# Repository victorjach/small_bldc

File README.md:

small_bldc
==========

Small Brushless Motor controller

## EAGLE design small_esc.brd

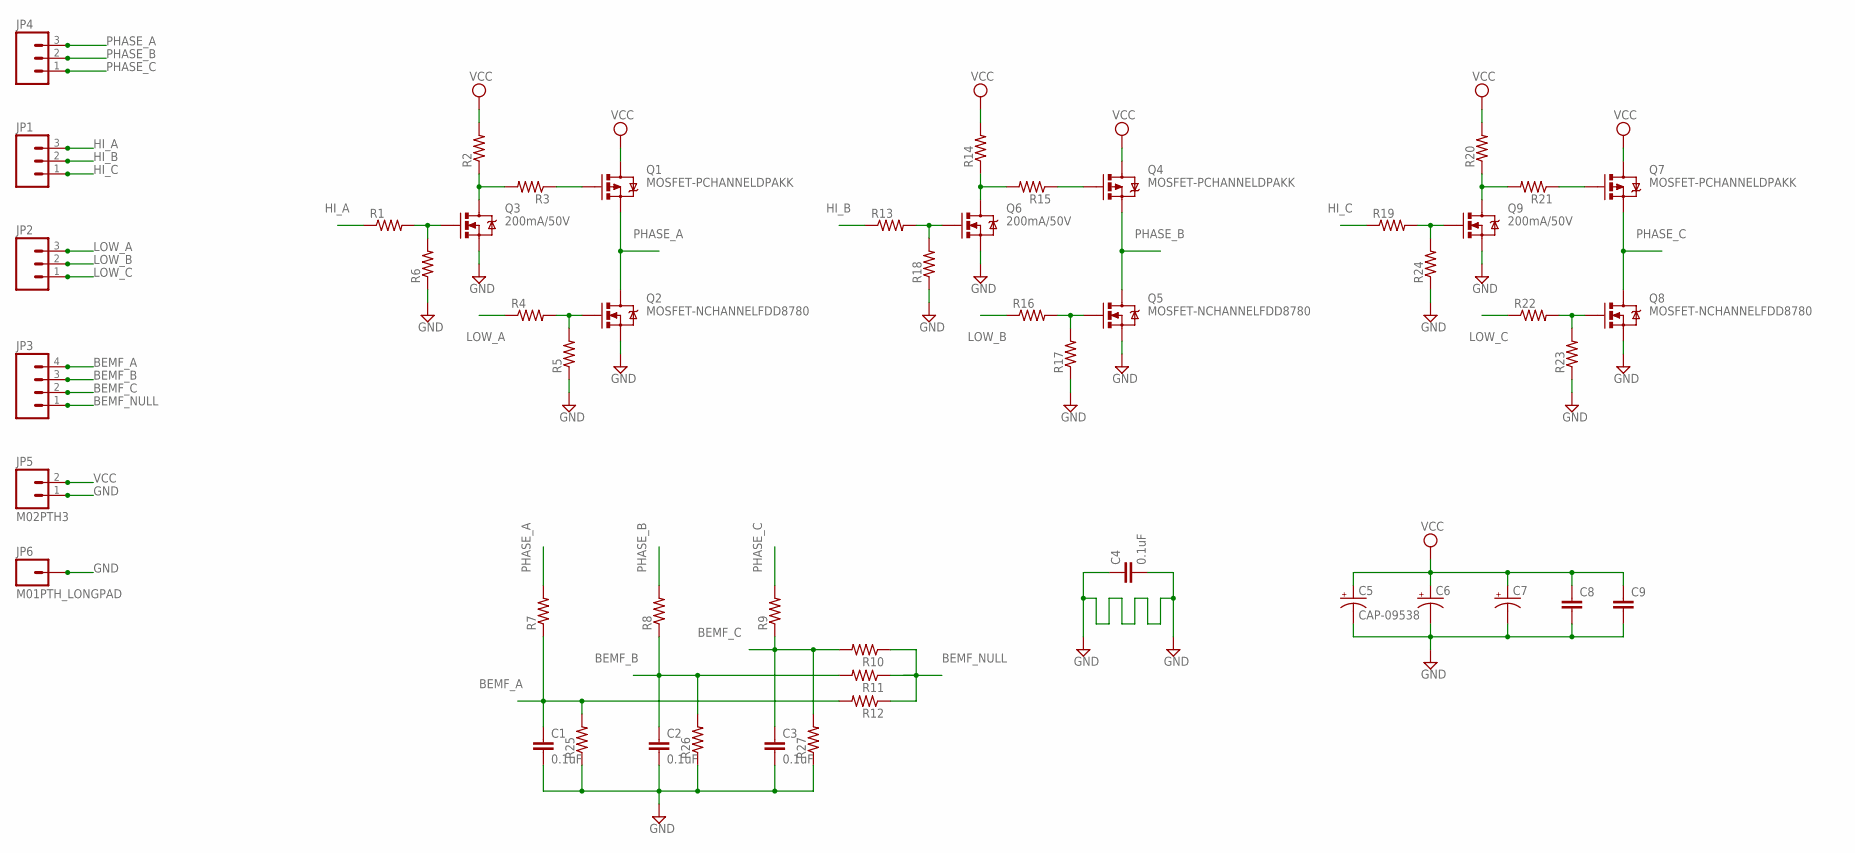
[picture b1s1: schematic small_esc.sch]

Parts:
C1, C2, C3, C4: 0.1uF; 0603-CAP
C5: CAP-09538; CPOL-RADIAL-1000UF-25V
C6, C7: CAP_POLPTH2; CPOL-RADIAL-10UF-25V
C8, C9: 0.1UF-50V-20%(PTH)KIT-EZ; CAP-PTH-SMALL-KIT
JP1, JP2, JP4: M03LONGPADS; 1X03_LONGPADS
JP3: M04LONGPADS; 1X04_LONGPADS
JP5: M02PTH3; 1X02_LONGPADS
JP6: M01PTH_LONGPAD; 1X01_LONGPAD
Q1, Q4, Q7: MOSFET-PCHANNELDPAKK; DPAK
Q2, Q5, Q8: MOSFET-NCHANNELFDD8780; DPAK
Q3, Q6, Q9: 200mA/50V; SOT23-3
R1, R2, R3, R4, R5, R6, R7, R8, R9, R10, R11, R12, R13, R14, R15, R16, R17, R18, R19, R20, R21, R22, R23, R24, R25, R26, R27: RESISTOR0603; 0603-RES

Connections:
BEMF_A: C1.1, JP3.4, R7.1, R12.2, R25.2
BEMF_B: C2.1, JP3.3, R8.1, R11.2, R26.2
BEMF_C: C3.1, JP3.2, R9.1, R10.2, R27.2
BEMF_NULL: JP3.1, R10.1, R11.1, R12.1
GND: C1.2, C2.2, C3.2, C4.1, C4.2, C5.-, C6.2 (-), C7.2 (-), C8.2, C9.2, JP5.1, JP6.1, Q2.3 (S), Q3.2 (S), Q5.3 (S), Q6.2 (S), Q8.3 (S), Q9.2 (S), R5.1, R6.1, R17.1, R18.1, R23.1, R24.1, R25.1, R26.1, R27.1
HI_A: JP1.3, R1.1
HI_B: JP1.2, R13.1
HI_C: JP1.1, R19.1
LOW_A: JP2.3, R4.1
LOW_B: JP2.2, R16.1
LOW_C: JP2.1, R22.1
unnamed: Q1.1 (G), R3.1
unnamed: Q3.3 (D), R2.1, R3.2
unnamed: Q3.1 (G), R1.2, R6.2
unnamed: Q2.1 (G), R4.2, R5.2
unnamed: Q4.1 (G), R15.1
unnamed: Q6.3 (D), R14.1, R15.2
unnamed: Q6.1 (G), R13.2, R18.2
unnamed: Q5.1 (G), R16.2, R17.2
unnamed: Q7.1 (G), R21.1
unnamed: Q9.3 (D), R20.1, R21.2
unnamed: Q9.1 (G), R19.2, R24.2
unnamed: Q8.1 (G), R22.2, R23.2
PHASE_A: JP4.3, Q1.4 (S), Q2.4 (D), R7.2
PHASE_B: JP4.2, Q4.4 (S), Q5.4 (D), R8.2
PHASE_C: JP4.1, Q7.4 (S), Q8.4 (D), R9.2
VCC: C5.+, C6.1 (+), C7.1 (+), C8.1, C9.1, JP5.2, Q1.3 (D), Q4.3 (D), Q7.3 (D), R2.2, R14.2, R20.2

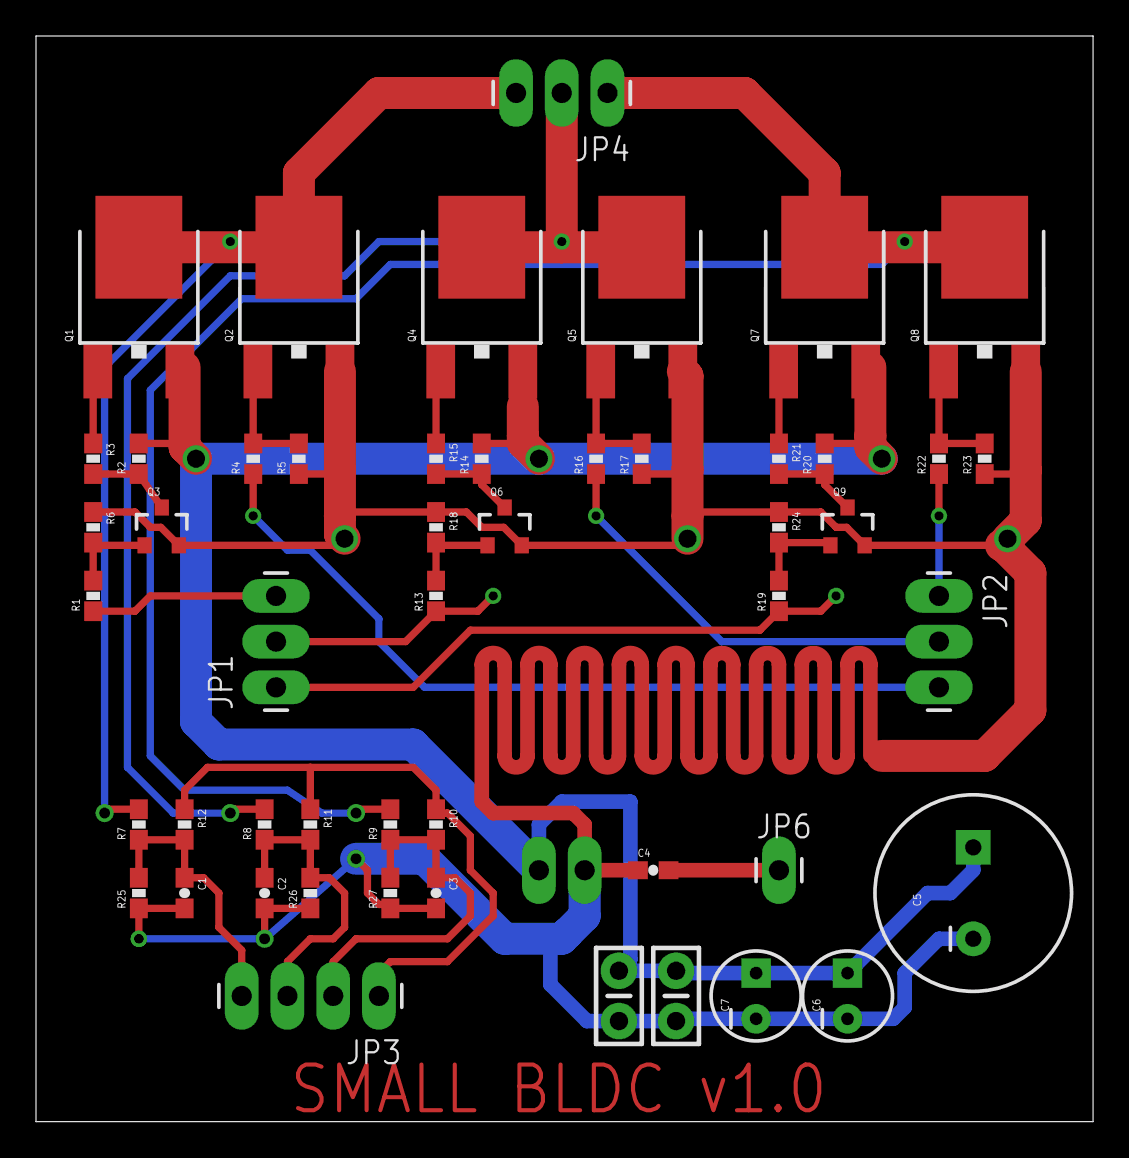
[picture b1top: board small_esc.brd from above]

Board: 2 copper layers, 58.7 x 60.3 mm, 51 parts (0 on the bottom side), 27 nets.

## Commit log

2014-12-22 Initial state of the project
2014-12-22 add bypass capacitors

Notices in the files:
parts and their libraries:
SparkFun-DiscreteSemi: Licensing: Creative Commons ShareAlike 4.0 International - https://creativecommons.org/licenses/by-sa/4.0
